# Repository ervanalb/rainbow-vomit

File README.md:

# Rainbow Vomit
The stupid simple WS2812 driver

## Why?
I wanted to drive WS2812 LEDs from a computer. For some reason that's not a solved problem?

## What?
Pixels get clocked at 800 kbps, and each pixel is 24 bits.
If you want a 30 Hz refresh rate, you should be able to drive smooth video to a strand of 1024 pixels.

I want a USB interface, and USB FS can do 12 mbps. So that means I should be able to run about 8 channels at 800 kbps with some room for overhead.

So I should be able to run smooth video on a 8192 LED setup without even diving into high speed USB.

For some reason, most simple drivers can't come close to these specs. Respect for the [Pixel Pusher](http://www.heroicrobotics.com/products/pixelpusher) though, it's just large, expensive, and uses Ethernet.

## How?
I tricked the STM32F105 into doing this for me. It took a lot of fiddling with the DMA engine and USB peripheral. It's an extension of the approach [here](https://github.com/ervanalb/lux/blob/master/led_strip_firmware/app/src/ws2811_strip.c) to 8 channels (all four channels on two timers.)

I've included a [binary](driver-firmware/rainbow-vomit-driver.bin) in the git repository because the timing is very finicky and you may not get full speed on your compiler.

## Anything else?
Why yes, thanks for asking.

You may not want your display topology to require daisy-chaining LEDs together until you reach 1000 pixels.
So, I'm going to make a multiplexer board that splits a single channel into N strips.
It will distribute pixels round-robin to all the connected strips so you can use more of a star topology in your setup.
This will operate entirely on the WS2812 protocol, so you can use any driver, not just mine.

I also find it weird that this doesn't exist yet.

## Now what?
Maybe Adafruit or Sparkfun will steal my design and mass produce it. That would be cool.

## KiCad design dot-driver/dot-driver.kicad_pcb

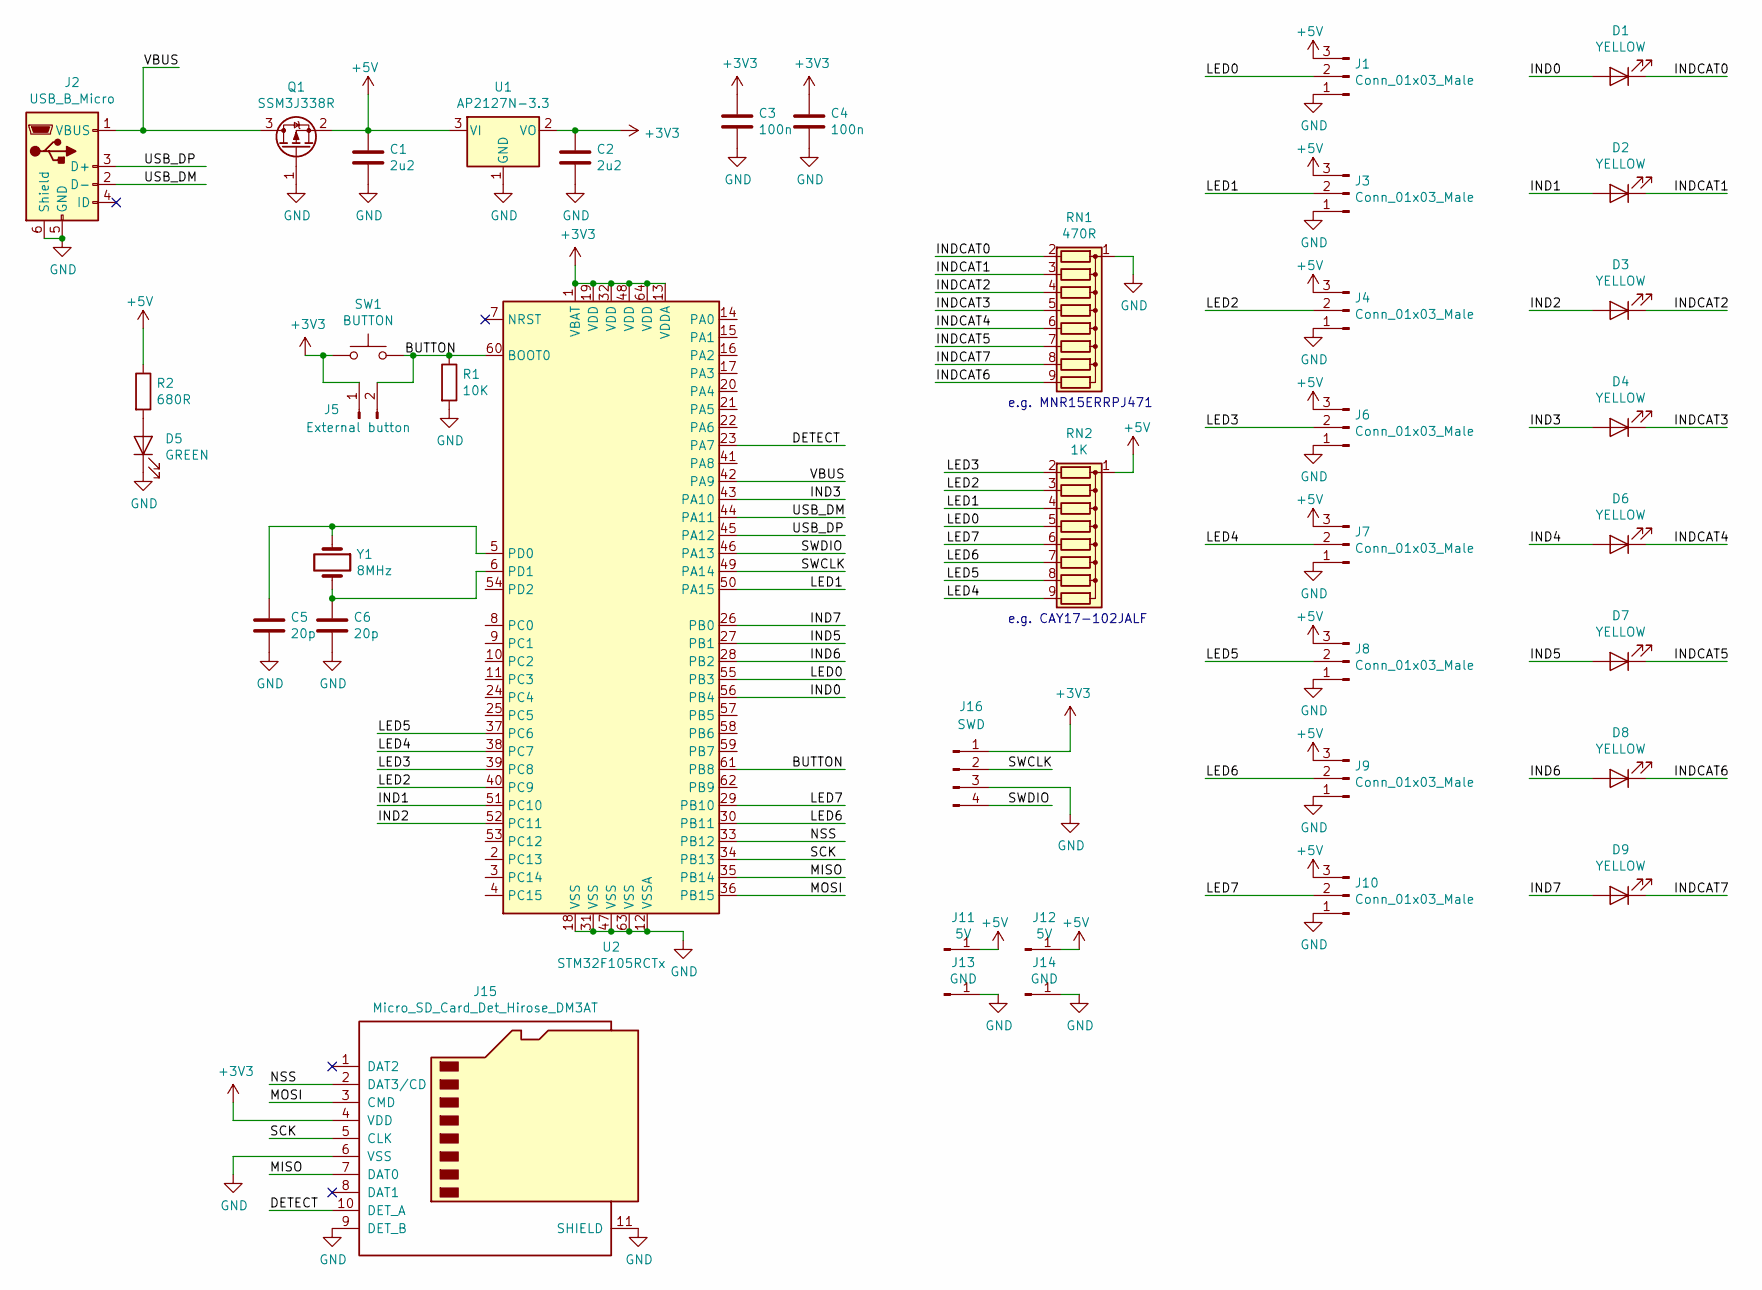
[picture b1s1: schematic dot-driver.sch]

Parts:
C1, C2: 2u2; C_0603
C3, C4: 100n; C_0603
C5, C6: 20p; C_0603
D1, D2, D3, D4, D6, D7, D8, D9: YELLOW; LED_0603
D5: GREEN; LED_0603
J1, J3, J4, J6, J7, J8, J9, J10: Conn_01x03_Male; Pin_Header_Straight_1x03
J2: USB_B_Micro; USB_Micro-B
J5: External button; Pin_Header_Straight_1x02
J11, J12: 5V; Pin_Header_Straight_1x01
J13, J14: GND; Pin_Header_Straight_1x01
J15: Micro_SD_Card_Det_Hirose_DM3AT; microSD_HC_Hirose_DM3AT-SF-PEJM5
J16: SWD; Pin_Header_Straight_1x04
Q1: SSM3J338R; SOT-23
R1: 10K; R_0603
R2: 680R; R_0603
RN1: 470R; R_Array_Convex_5x0603
RN2: 1K; R_Array_Convex_5x0603
SW1: BUTTON; SW_SPST_TL3342
U1: AP2127N-3.3; SOT-23
U2: STM32F105RCTx; LQFP-64_10x10mm_Pitch0.5mm
Y1: 8MHz; Crystal_SMD_5032_4Pads

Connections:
+3V3: C2.1, C3.1, C4.1, J5.1, J15.4 (VDD), J16.1, SW1.1, U1.2 (VO), U2.1 (VBAT), U2.13 (VDDA), U2.19 (VDD), U2.32 (VDD), U2.48 (VDD), U2.64 (VDD)
+5V: C1.1, J1.3, J3.3, J4.3, J6.3, J7.3, J8.3, J9.3, J10.3, J11.1, J12.1, Q1.2 (S), R2.1, RN2.1 (common), U1.3 (VI)
/BUTTON: J5.2, R1.1, SW1.2, U2.60 (BOOT0), U2.61 (PB8)
/DETECT: J15.10 (DET_A), U2.23 (PA7)
/IND0: D1.2 (A), U2.56 (PB4)
/IND1: D2.2 (A), U2.51 (PC10)
/IND2: D3.2 (A), U2.52 (PC11)
/IND3: D4.2 (A), U2.43 (PA10)
/IND4: D6.2 (A)
/IND5: D7.2 (A), U2.27 (PB1)
/IND6: D8.2 (A), U2.28 (PB2)
/IND7: D9.2 (A), U2.26 (PB0)
/INDCAT0: D1.1 (K), RN1.2 (R1)
/INDCAT1: D2.1 (K), RN1.3 (R2)
/INDCAT2: D3.1 (K), RN1.4 (R3)
/INDCAT3: D4.1 (K), RN1.5 (R4)
/INDCAT4: D6.1 (K), RN1.6 (R5)
/INDCAT5: D7.1 (K), RN1.7 (R6)
/INDCAT6: D8.1 (K), RN1.9 (R8)
/INDCAT7: D9.1 (K), RN1.8 (R7)
/LED0: J1.2, RN2.5 (R4), U2.55 (PB3)
/LED1: J3.2, RN2.4 (R3), U2.50 (PA15)
/LED2: J4.2, RN2.3 (R2), U2.40 (PC9)
/LED3: J6.2, RN2.2 (R1), U2.39 (PC8)
/LED4: J7.2, RN2.9 (R8), U2.38 (PC7)
/LED5: J8.2, RN2.8 (R7), U2.37 (PC6)
/LED6: J9.2, RN2.7 (R6), U2.30 (PB11)
/LED7: J10.2, RN2.6 (R5), U2.29 (PB10)
/MISO: J15.7 (DAT0), U2.35 (PB14)
/MOSI: J15.3 (CMD), U2.36 (PB15)
/NSS: J15.2 (DAT3/CD), U2.33 (PB12)
/SCK: J15.5 (CLK), U2.34 (PB13)
/SWCLK: J16.2, U2.49 (PA14)
/SWDIO: J16.4, U2.46 (PA13)
/USB_DM: J2.2 (D-), U2.44 (PA11)
/USB_DP: J2.3 (D+), U2.45 (PA12)
/VBUS: J2.1 (VBUS), Q1.3 (D), U2.42 (PA9)
GND: C1.2, C2.2, C3.2, C4.2, C5.2, C6.2, D5.1 (K), J1.1, J2.5 (GND), J2.6 (Shield), J3.1, J4.1, J6.1, J7.1, J8.1, J9.1, J10.1, J13.1, J14.1, J15.6 (VSS), J15.9 (DET_B), J15.11 (SHIELD), J16.3, Q1.1 (G), R1.2, RN1.1 (common), U1.1 (GND), U2.12 (VSSA), U2.18 (VSS), U2.31 (VSS), U2.47 (VSS), U2.63 (VSS)
unnamed: C5.1, U2.5 (PD0), Y1.1
unnamed: C6.1, U2.6 (PD1), Y1.2
unnamed: D5.2 (A), R2.2

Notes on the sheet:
e.g. MNR15ERRPJ471
e.g. CAY17-102JALF

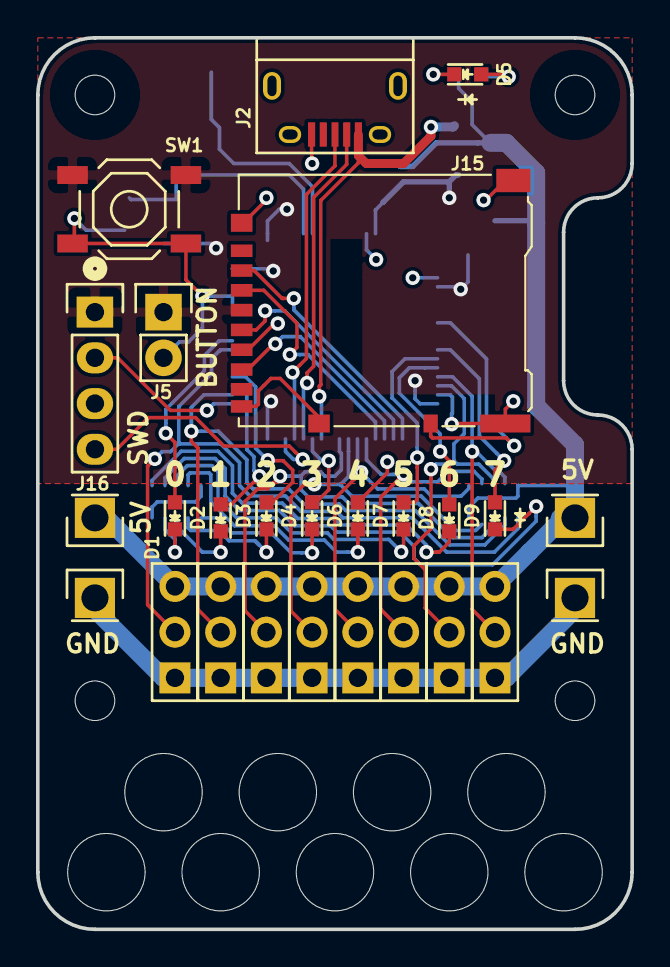
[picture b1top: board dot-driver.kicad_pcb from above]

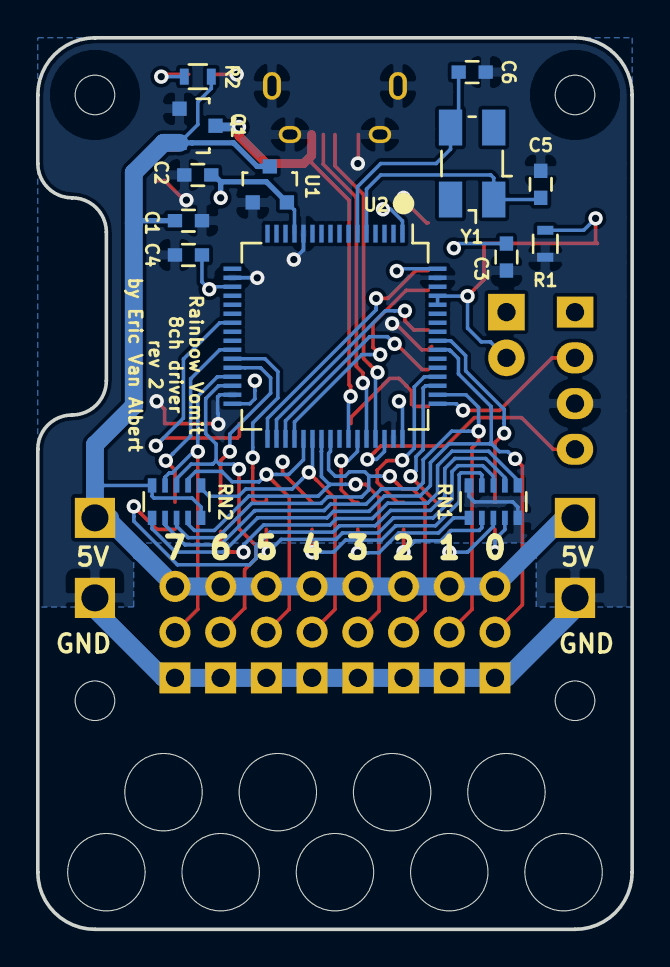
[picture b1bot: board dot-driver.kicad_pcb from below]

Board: 2 copper layers, 33.0 x 49.5 mm, 40 parts (14 on the bottom side), 40 nets.

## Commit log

2018-11-13 add schematics
2018-11-13 Add gerbers
2018-11-13 write snarky readme
2018-11-13 fix mistakes in snarky readme
2019-01-09 start working on output ability
2019-01-09 first commit of firmware I guess?
2019-01-11 implement double buffering
2019-01-11 copy in lux code for output (need to port to libopencm3)
2019-01-11 Port to openCM3 (untested)
2019-01-12 ch0 output working
2019-01-12 four channels almost working
2019-01-12 Fix DMA alignment problem
2019-01-12 four channels working
2019-01-12 all channels working
2019-01-12 consolidate a function
2019-01-12 add some debugging lights to aid in optimization
2019-01-13 Allow for -flto but don't use it
2019-01-13 Fixed USB speed, now need to improve protocol decode speed
2019-01-13 add opencm3 as a submodule
2019-01-13 Writing at full speed
2019-01-13 it stopped working and I'm not sure why
2019-01-14 woo, working! moved to back using -flto to get the last burst of speed
2019-01-14 rewrite protocol document
2019-01-14 fix table formatting in protocol document
2020-03-07 Start adding SPI HAL
2020-03-07 fill out more SD api
2020-03-07 Add ChaN's FatFS, and fix warnings
2020-03-10 Working but very fragile SD code
2020-03-10 Output seems to be working even with extra delay in output_write
2020-03-12 Fix DMA AHB contention problems
2020-03-12 Move SD startup code to autorun.c, move indicator lights to interrupt, remove 1 NOP
2020-03-12 Add frame timing to SD card with systick
2020-03-12 Add SD card section to protocol
2020-03-13 Fix SD clock frequencies, and implement a slightly improved multi-byte transfer function
2020-03-15 Improve schematic and layout, but they are out of sync
2020-03-15 Route rev2 of driver board
2020-03-16 Generate rev2 gerbers
2022-06-10 Begin work on static pattern for firefly
2022-06-15 nice pattern
